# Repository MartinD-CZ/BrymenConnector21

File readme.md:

# Brymen 867/869 adapter cable rev2.1
*see the article [here](http://embedblog.eu/?p=830) or the listing [here](https://www.tindie.com/products/martind/brymen-867869-adapter-cable/)*

## Features
- reads data from Brymen 867/869 via infrared
- sends the measurements at 115200 baud via serial port
- output data rate and format adjustable (5 readings/s, 1 reading/s, single reading); settings are stored in EEPROM and remembered on next power up
- BOOT0 pin available as a button, so you can update the FW without disassembling the case
- activity LED

*Here's how the serial output looks:*

*If you are ordering it without the USB cable, here's how to connect it:*

*Note: revisions 1.x can be found [here](https://github.com/MartinD-CZ/brymen-867-interface-cable/blob/master/README.md), revision 2.0 can be found [here](https://github.com/MartinD-CZ/brymen-867-869-interface-cable-rev20).*

*And here's the schematic:*

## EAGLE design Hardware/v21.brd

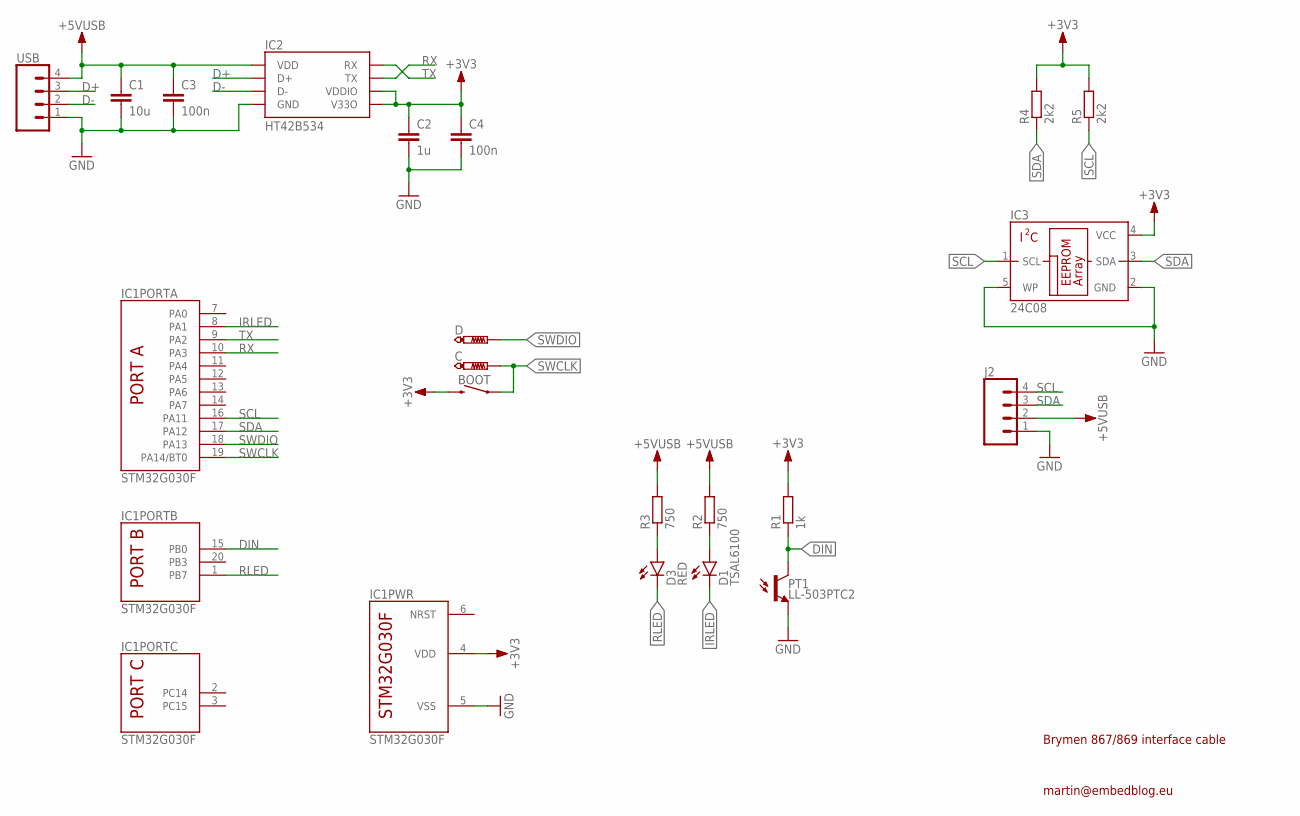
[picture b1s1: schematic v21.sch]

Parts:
BOOT: MOMENTARY-SWITCH-SPST-SMD-5.2MM; TACTILE_SWITCH_SMD_5.2MM
C: PTR1B1,27; B1,27
C1: 10u; C0603
C2: 1u; C0603
C3, C4: 100n; C0603
D: PTR1B1,27; B1,27
D1: TSAL6100; LED_5MM
D3: RED; LED-0603; LCSC# C2286
IC1: STM32G030F; TSSOP20
IC2: HT42B534; SOP8
IC3: 24C08; SOT23-5
J2: CONN_041.27MM; 1X04_1.27MM
PT1: LL-503PTC2; LED5MM
R1: 1k; R0603
R2, R3: 750; R0603
R4, R5: 2k2; R0603
USB: CONN_04; 1X04

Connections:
+3V3: BOOT.3 (2), C2.1, C4.1, IC1.4 (VDD), IC2.3 (VDDIO), IC2.8 (V33O), IC3.4 (VCC), R1.2, R4.2, R5.2
+5VUSB: C1.1, C3.1, IC2.7 (VDD), J2.2, R2.2, R3.2, USB.4
D+: IC2.5 (D+), USB.3
D-: IC2.6 (D-), USB.2
DIN: IC1.15 (PB0), PT1.K (C), R1.1
GND: C1.2, C2.2, C3.2, C4.2, IC1.5 (VSS), IC2.1 (GND), IC3.2 (GND), IC3.5 (WP), J2.1, PT1.A (E), USB.1
IRLED: D1.K (C), IC1.8 (PA1)
unnamed: D1.A, R2.1
unnamed: D3.A, R3.1
RLED: D3.C, IC1.1 (PB7)
RX: IC1.10 (PA3), IC2.2 (TX)
SCL: IC1.16 (PA11), IC3.1 (SCL), J2.4, R5.1
SDA: IC1.17 (PA12), IC3.3 (SDA), J2.3, R4.1
SWCLK: BOOT.1, C.TP, IC1.19 (PA14/BT0)
SWDIO: D.TP, IC1.18 (PA13)
TX: IC1.9 (PA2), IC2.4 (RX)

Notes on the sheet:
Brymen 867/869 interface cable
martin@embedblog.eu

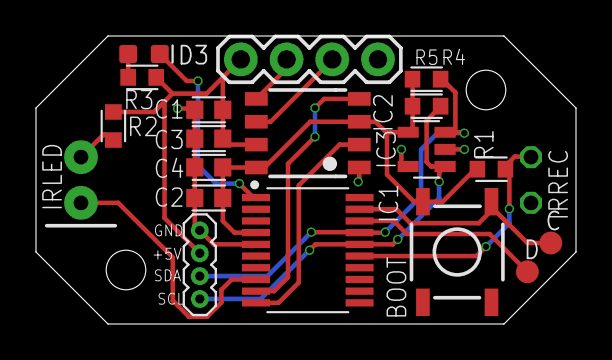
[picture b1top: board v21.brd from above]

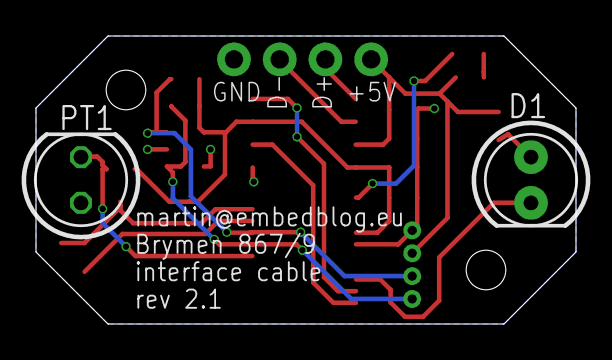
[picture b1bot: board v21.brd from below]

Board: 2 copper layers, 30.0 x 16.0 mm, 20 parts (2 on the bottom side), 16 nets.

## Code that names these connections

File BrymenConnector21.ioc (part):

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Mcu.Name=STM32G030F6Px
Mcu.Package=TSSOP20
Mcu.UserName=STM32G030F6Px
PA1.GPIOParameters=PinState,GPIO_PuPd,GPIO_Label,GPIO_ModeDefaultOutputPP
PA1.GPIO_Label=IRLED
PA1.GPIO_ModeDefaultOutputPP=GPIO_MODE_OUTPUT_OD
PA1.GPIO_PuPd=GPIO_NOPULL
PA1.PinState=GPIO_PIN_SET
PA1.Signal=GPIO_Output
PA11\ [PA9].Mode=I2C
PA11\ [PA9].Signal=I2C2_SCL
PA12\ [PA10].Mode=I2C
PA12\ [PA10].Signal=I2C2_SDA
PA13.Mode=Serial_Wire
PA13.Signal=SYS_SWDIO
PA14-BOOT0.Mode=Serial_Wire
PA14-BOOT0.Signal=SYS_SWCLK
PA2.Mode=Asynchronous
PA2.Signal=USART2_TX
PA3.Mode=Asynchronous
PA3.Signal=USART2_RX
PB0.GPIOParameters=GPIO_Label
PB0.GPIO_Label=DIN
PB0.Signal=GPIO_Input
PB7.GPIOParameters=PinState,GPIO_PuPd,GPIO_Label,GPIO_ModeDefaultOutputPP
PB7.GPIO_Label=REDLED
PB7.GPIO_ModeDefaultOutputPP=GPIO_MODE_OUTPUT_OD
PB7.GPIO_PuPd=GPIO_NOPULL
PB7.PinState=GPIO_PIN_SET
PB7.Signal=GPIO_Output
RCC.HSE_VALUE=8000000
RCC.SYSCLKFreq_VALUE=8000000
board=custom

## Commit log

2022-03-07 added HalUtils submodule
2022-03-07 added Eeprom24 submodule
2022-03-07 compilation errors
2022-03-07 fixed compilation errors
2022-03-07 eeprom tested
2022-03-07 added comport & idle line callback
2022-03-08 added comport command interpreter
2022-03-08 added git info
2022-03-08 added Release configuration
2022-03-08 updated gitignore
2022-03-08 Remove ignored files
2022-03-08 switched printf to static buffer
2022-03-08 updated webpage
2022-03-09 fixed red led bug, moved order of init
2022-03-09 added release run configuration
2022-03-09 reworked superloop
2022-03-09 updated default GPIO values
2022-03-09 updated timer enable to speed up clock
2022-03-09 added info about 5 Hz mode; improved delay between 1 Hz readings
2022-03-09 eeprom bugfix
2022-03-09 added comport confirmation msgs
2022-03-09 updated article URL
2022-03-09 added hardware folder

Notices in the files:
parts and their libraries:
SparkFun-LED: Licensing: Creative Commons ShareAlike 4.0 International - https://creativecommons.org/licenses/by-sa/4.0
